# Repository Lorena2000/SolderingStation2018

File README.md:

# SolderingStation2018

I’m an apprentice who works in Switzerland and tried to build the soldering station. 
Unfortunatly it doesen't worked, and i had made some changes. 
I like to offer you the changes that not everyone has to find out them by themself. 

At first the Arduino pro mini with the correct pin assignment couldn’t be delivered, it
was an old version and the companies who sold them, doesn’t deliver anything to
Switzerland. So I draw a new eagle file, I just changed the Arduino mini with
an Arduino Nano. Later when everything worked I made some more changes, the
reset wasn’t connected, added a GND connection and change the connection of the
Potentiometer. 

I found the correct display for the station but the program doesn’t work on the new Arduino
version (1.8.5). But the display needs the new version to work, so I debugged
the program with help from an informatics student. 

Because I changed the Arduino and some other components I also had to change the 3D
components, but with the new version of Inventor I couldn’t import the stl.
files so I draw new ones. 

You could find the Programm, the New Stl. files, the new Arduino board with the shema and a partlist.

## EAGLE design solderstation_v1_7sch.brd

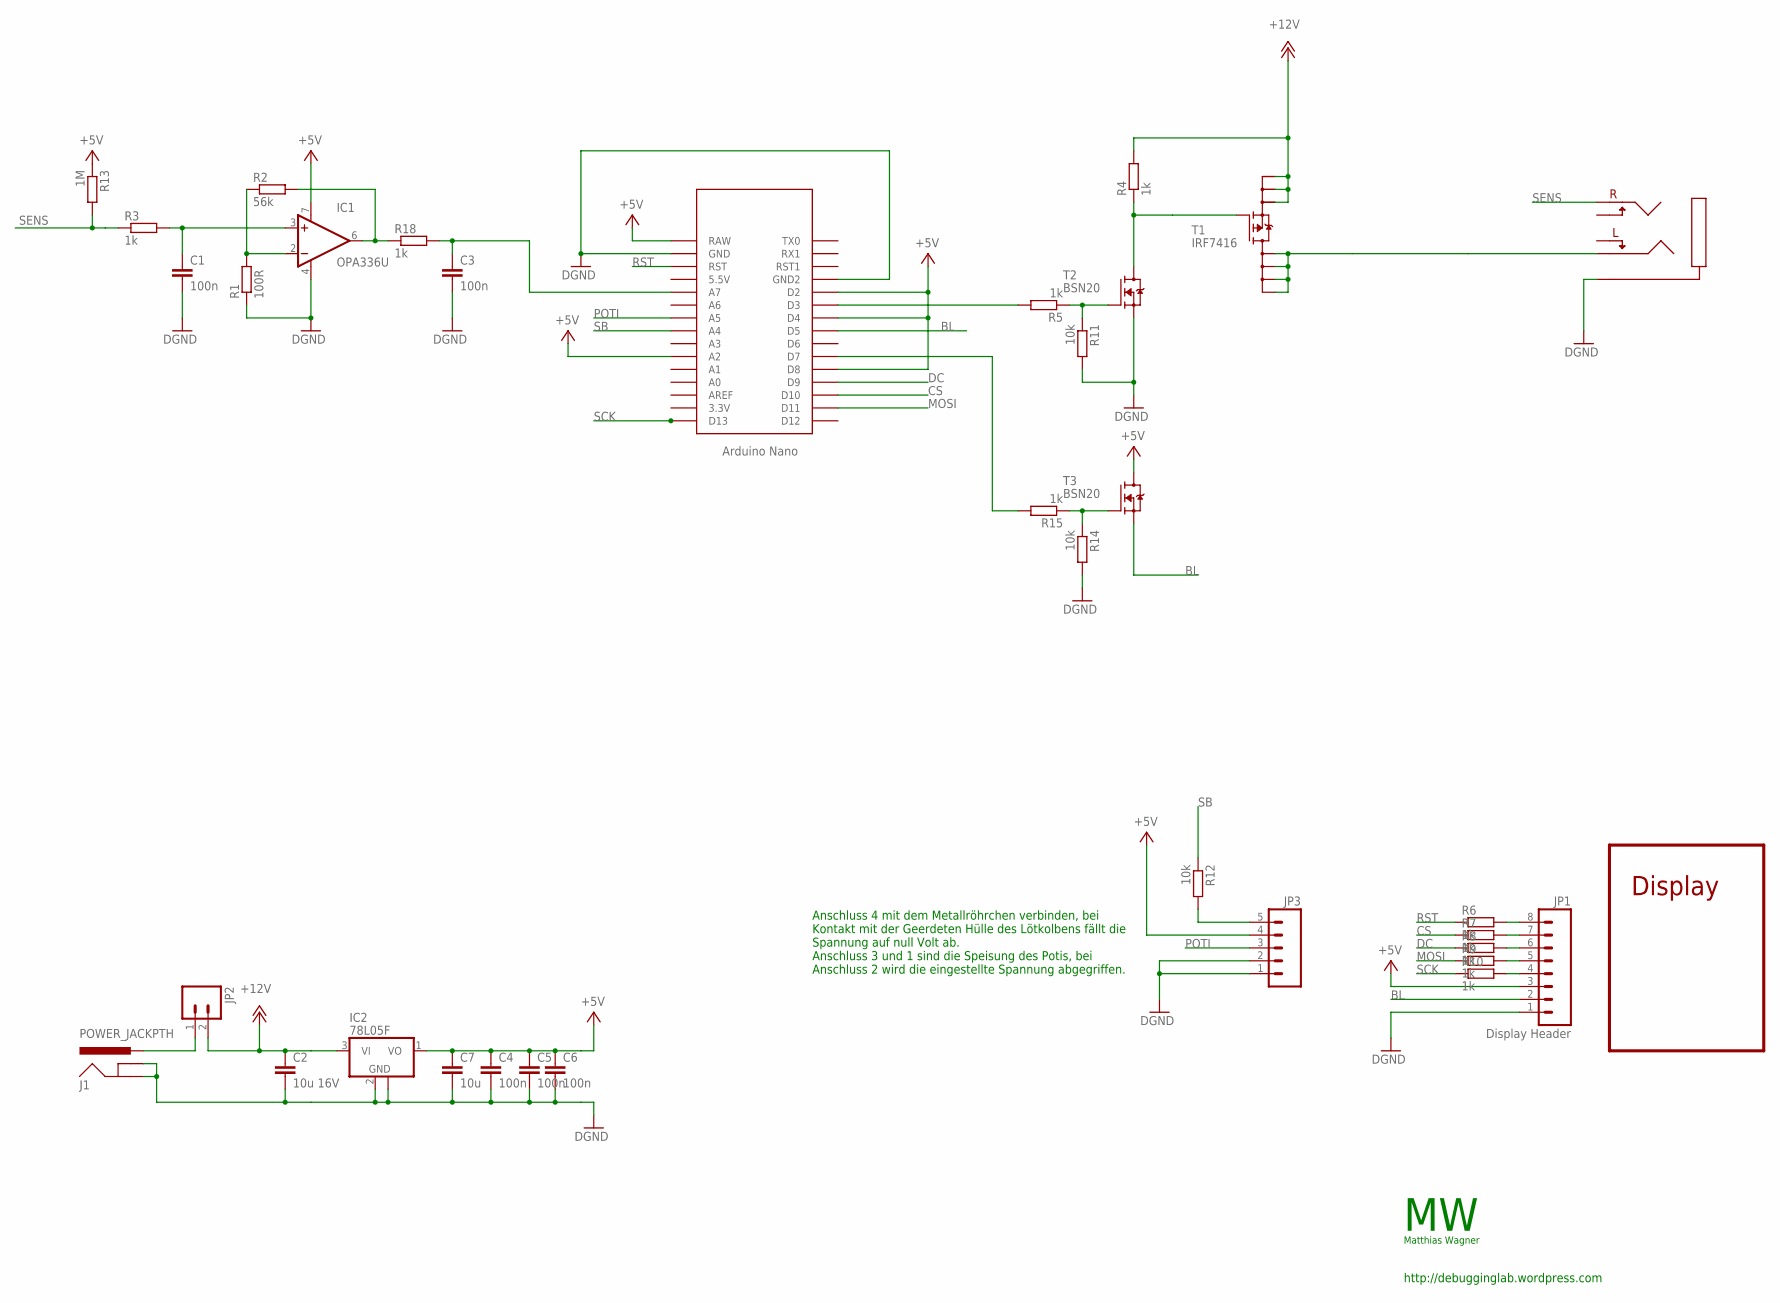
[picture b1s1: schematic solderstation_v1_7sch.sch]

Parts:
C1, C3, C4, C5, C6: 100n; C0603
C2: 10u 16V; C1206
C7: 10u; C1206
IC1: OPA336U; SO08
IC2: 78L05F; SOT89
J1: POWER_JACKPTH; POWER_JACK_PTH
JP1: Display Header; 1X08_LOCK
JP2: M02LOCK_LONGPADS; 1X02_LOCK_LONGPADS
JP3: M05; 05P
R1: 100R; R0603
R2: 56k; R0603
R3, R4, R5, R6, R7, R8, R9, R10, R15, R18: 1k; R0603
R11, R12, R14: 10k; R0603
R13: 1M; R0603
T1: IRF7416; SO8
T2, T3: BSN20; SOT23
U$1: NANO
U$2: AUDIO_JACK_3,5MMCONRAD; AUDIO_JACK_3,5MM_CONRAD

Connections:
+5V: C4.1, C5.1, C6.1, C7.1, IC1.7 (V+), IC2.1 (VO), JP1.3, JP3.4, R13.1, T3.3 (D), U$1.A2, U$1.D2, U$1.D4, U$1.D8, U$1.RAW
+12V: C2.1, IC2.3 (VI), JP2.2, R4.2, T1.1 (S0), T1.2 (S1), T1.3 (S2)
BL: JP1.2, T3.2 (S), U$1.D5
CS: R7.1, U$1.D10
DC: R8.1, U$1.D9
DGND: C1.2, C2.2, C3.2, C4.2, C5.2, C6.2, C7.2, IC1.4 (V-), IC2.2 (GND), IC2.2@1 (GND), J1.GND, J1.GNDBREAK, JP1.1, JP3.1, JP3.2, R1.1, R11.2, R14.2, T2.2 (S), U$1.GND, U$1.GND1 (GND2), U$2.P_GND
HEATER: T1.5 (D0), T1.6 (D1), T1.7 (D2), T1.8 (D3), U$2.P_LEFT
MOSI: R9.1, U$1.D11
unnamed: IC1.2 (-IN), R1.2, R2.1
unnamed: IC1.6 (OUT), R2.2, R18.1
unnamed: R5.1, R11.1, T2.1 (G)
unnamed: C1.1, IC1.3 (+IN), R3.2
unnamed: R4.1, T1.4 (G), T2.3 (D)
unnamed: JP1.4, R10.2
unnamed: R5.2, U$1.D3
unnamed: JP1.5, R9.2
unnamed: JP1.6, R8.2
unnamed: JP1.7, R7.2
unnamed: JP1.8, R6.2
unnamed: J1.PWR, JP2.1
unnamed: R14.1, R15.1, T3.1 (G)
unnamed: R15.2, U$1.D7
unnamed: JP3.5, R12.2
unnamed: C3.1, R18.2, U$1.A7
POTI: JP3.3, U$1.A5
RST: R6.1, U$1.RST
SB: R12.1, U$1.A4
SCK: R10.1, U$1.D13
SENS: R3.1, R13.2, U$2.P_RIGHT

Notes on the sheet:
Display
http://debugginglab.wordpress.com
Matthias Wagner
Anschluss 4 mit dem Metallröhrchen verbinden, bei Kontakt mit der Geerdeten Hülle des Lötkolbens fällt die Spannung auf null Volt ab. Anschluss 3 und 1 sind die Speisung des Potis, bei Anschluss 2 wird die eingestellte Spannung abgegriffen.

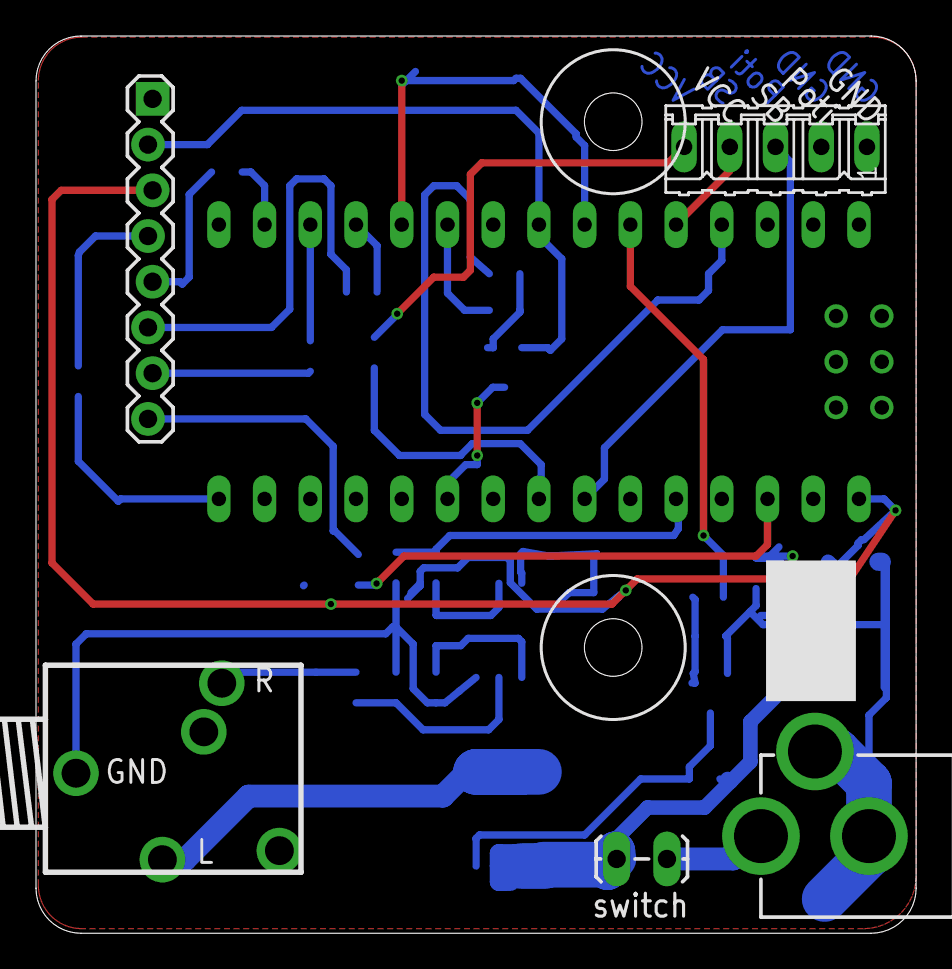
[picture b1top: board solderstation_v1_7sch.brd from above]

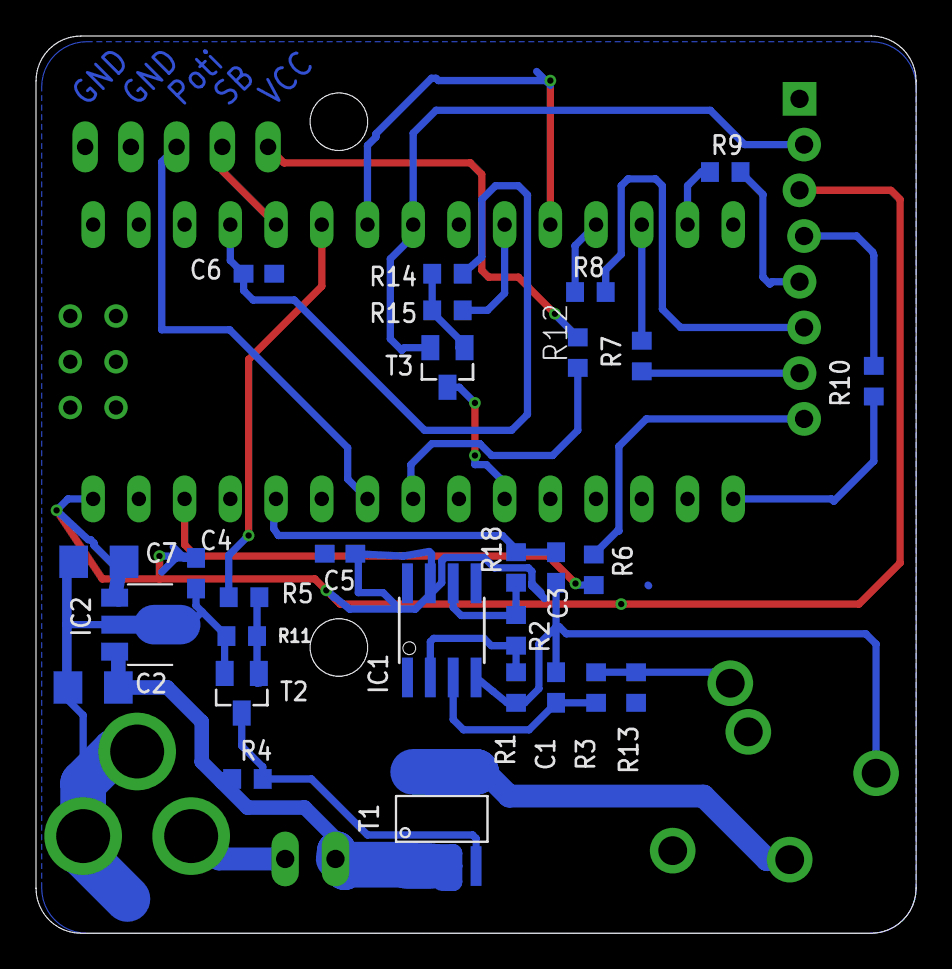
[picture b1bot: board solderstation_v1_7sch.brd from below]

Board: 2 copper layers, 48.9 x 49.8 mm, 34 parts (28 on the bottom side), 29 nets.

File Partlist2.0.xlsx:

| Soldering station 2018
 | I'm sorry that some names are in German that's because I order them in German a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
 | If you don’t understand it, just search for the articles on conrad.ch and then 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
 | I just wrote where i found the articles, perhaps you found them somewere cheape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
 | What | How many | Information | Where I have order it | Specificat information | Remark
 | Arduino Nano | 1 |  | Arduino.cc | https://store.arduino.cc/usa/arduino-nano
 | Potentiometer | 1 |  | conrad | Dreh Potentiometer Mono 0.25 W 10 kΩ | Artikel Nr. 9605
 | Switch | 1 |  | conrad | Wippschalter 12 V/DC 20 A | Artikel Nr. 700749Kfz
 | Power Supply | 1 |  | conrad | USB Ladegerät Goobay | Artikel Nr. 1602854 62
 | display | 1
 | OPA336U | 1 |  | Distrelec | Operationsverstärker zweifach 0.1 MHz | Artikel Nr. 30022737
 | 78L05F | 1 |  | Distrelec | Linearer Spannungsregler 5 V SOT-89-3, | Artikel Nr. 30018604
 | BSN20 | 2 |  | Distrelec | Kleinleistungstransistor SOT-23 N 50 V | Artikel Nr. 17101930
 | IRF7416 | 1 |  | conrad | MOSFET Infineon Technologies | Artikel Nr. IRF7416PBF
 | Power_JACKPTH | 1 |  | conrad | Niedervolt Steckverbinder Buchse | Artikel Nr. 735742
 | Klinkenbuchse ø 3.5 mm | 1 |  | conrad | Klinken Steckverbinder 3.5 mm Buchse | Artikel Nr. 734101
 | Soldering Iron | 1 |  | conrad | Lötspitze Nadelform Weller RT1 Spitzen Größe 0.2 mm | cost ca. 50 CHF
 | Klinken Steckverbinder 3.5 mm Buchse | 1 |  | conrad | KlinkenSteckverbinder 3.5 mm Stecker | Artikel Nr. NYS 231
 | Klinken-Steckverbinder 3.5 mm Stecker | 1 |  | conrad | Klinken Steckverbinder 3.5 mm Buchse | Artikel Nr. 595223
 | Mikrofonkabel 2 x 0.50 mm² | 3 m |  | conrad | Mikrofonkabel 2 x 0.50 mm² Schwarz LappKabel | Artikel Nr. 49900153
 | Resistor | 1 | 1MΩ | This was available in a intern lager at the company I worked for. | Form of structur 0603
 | Resistor | 10 | 1kΩ | " | "
 | Resistor | 1 | 100Ω | " | "
 | Resistor | 3 | 10kΩ | " | "
 | Resistor | 1 | 56kΩ | " | "
 | capacitor | 5 | 100nF | " | "
 | capacitor | 1 | 10µF 6V | " | "
 | capacitor | 1 | 10µF 16V | " | "
 |  |  |  | Written by Lorena Lötscher

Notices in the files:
parts and their libraries:
SparkFun: Licensing: CC v3.0 Share-Alike You are welcome to use this library for commercial purposes.
